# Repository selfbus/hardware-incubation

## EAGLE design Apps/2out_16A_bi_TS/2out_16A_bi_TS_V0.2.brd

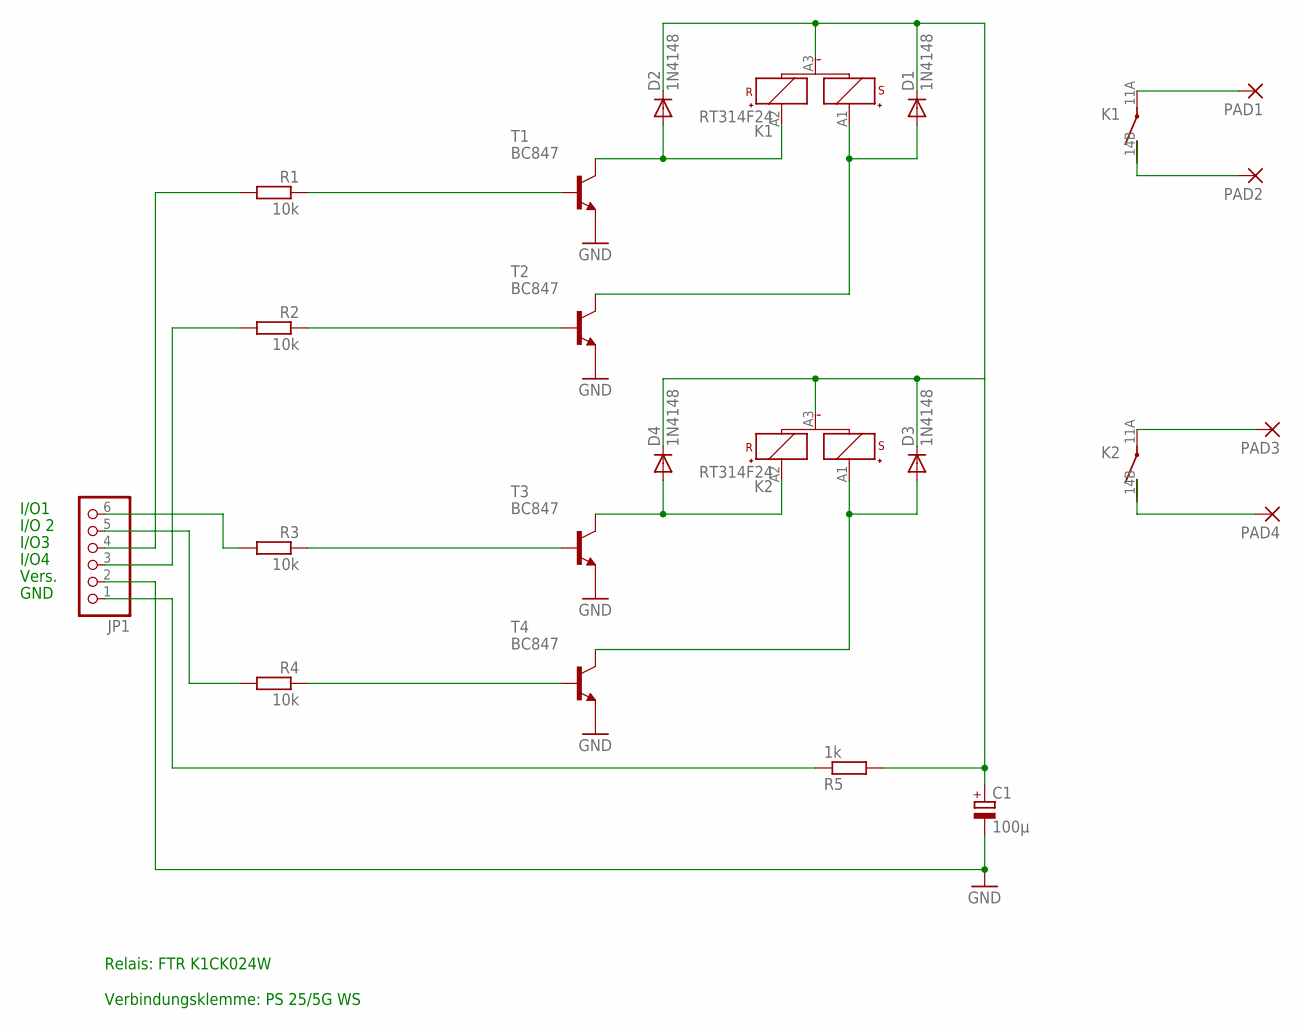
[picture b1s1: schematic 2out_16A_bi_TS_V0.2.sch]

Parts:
C1: 100µ; E3,5-8
D1, D2, D3, D4: 1N4148; MINIMELF
JP1: PINHD-1X6/90; 1X06/90
K1, K2: RT314F24; RT1-BI
PAD1, PAD2, PAD3, PAD4: 3,81/1,4
R1, R2, R3, R4: 10k; M1206
R5: 1k; M1206
T1, T2, T3, T4: BC847; SOT23

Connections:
GND: C1.-, JP1.2, T1.2 (E), T2.2 (E), T3.2 (E), T4.2 (E)
IO2: JP1.4, R1.2
unnamed: R2.1, T2.1 (B)
unnamed: JP1.3, R2.2
unnamed: K1.11A (PA), PAD1.1
unnamed: K1.14B (SA), PAD2.1
unnamed: K2.11A (PA), PAD3.1
unnamed: K2.14B (SA), PAD4.1
unnamed: JP1.6, R3.2
unnamed: R3.1, T3.1 (B)
unnamed: R4.1, T4.1 (B)
unnamed: JP1.5, R4.2
unnamed: R1.1, T1.1 (B)
unnamed: JP1.1, R5.1
R1: D1.A, K1.A1 (S+), T2.3 (C)
R2: D4.A, K2.A2 (R+), T3.3 (C)
R3: D2.A, K1.A2 (R+), T1.3 (C)
R4: D3.A, K2.A1 (S+), T4.3 (C)
VDD_IN: C1.+, D1.C, D2.C, D3.C, D4.C, K1.A3 (-), K2.A3 (-), R5.2

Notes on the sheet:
I/O1
Vers.
GND
Relais: FTR K1CK024W Verbindungsklemme: PS 25/5G WS
I/O 2
I/O3
I/O4

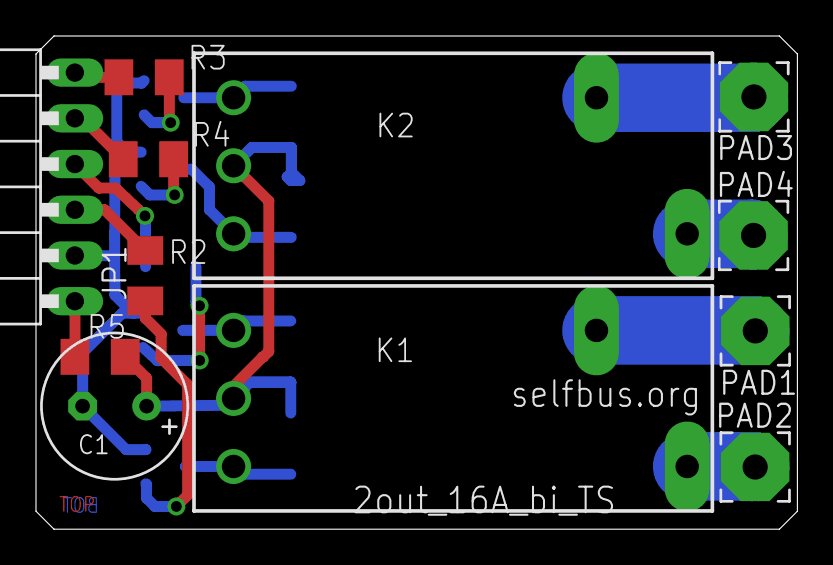
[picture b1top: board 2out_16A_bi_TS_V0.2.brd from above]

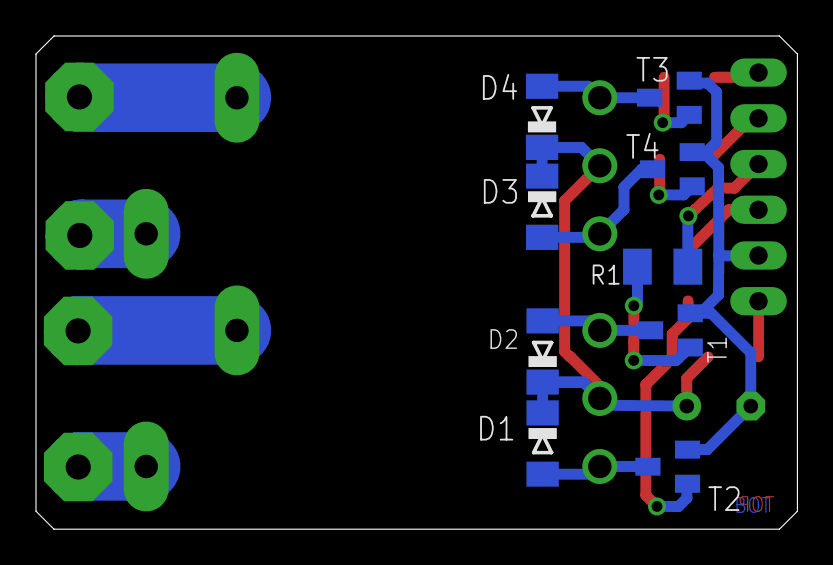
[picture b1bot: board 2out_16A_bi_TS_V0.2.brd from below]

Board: 2 copper layers, 42.3 x 27.4 mm, 21 parts (9 on the bottom side), 19 nets.

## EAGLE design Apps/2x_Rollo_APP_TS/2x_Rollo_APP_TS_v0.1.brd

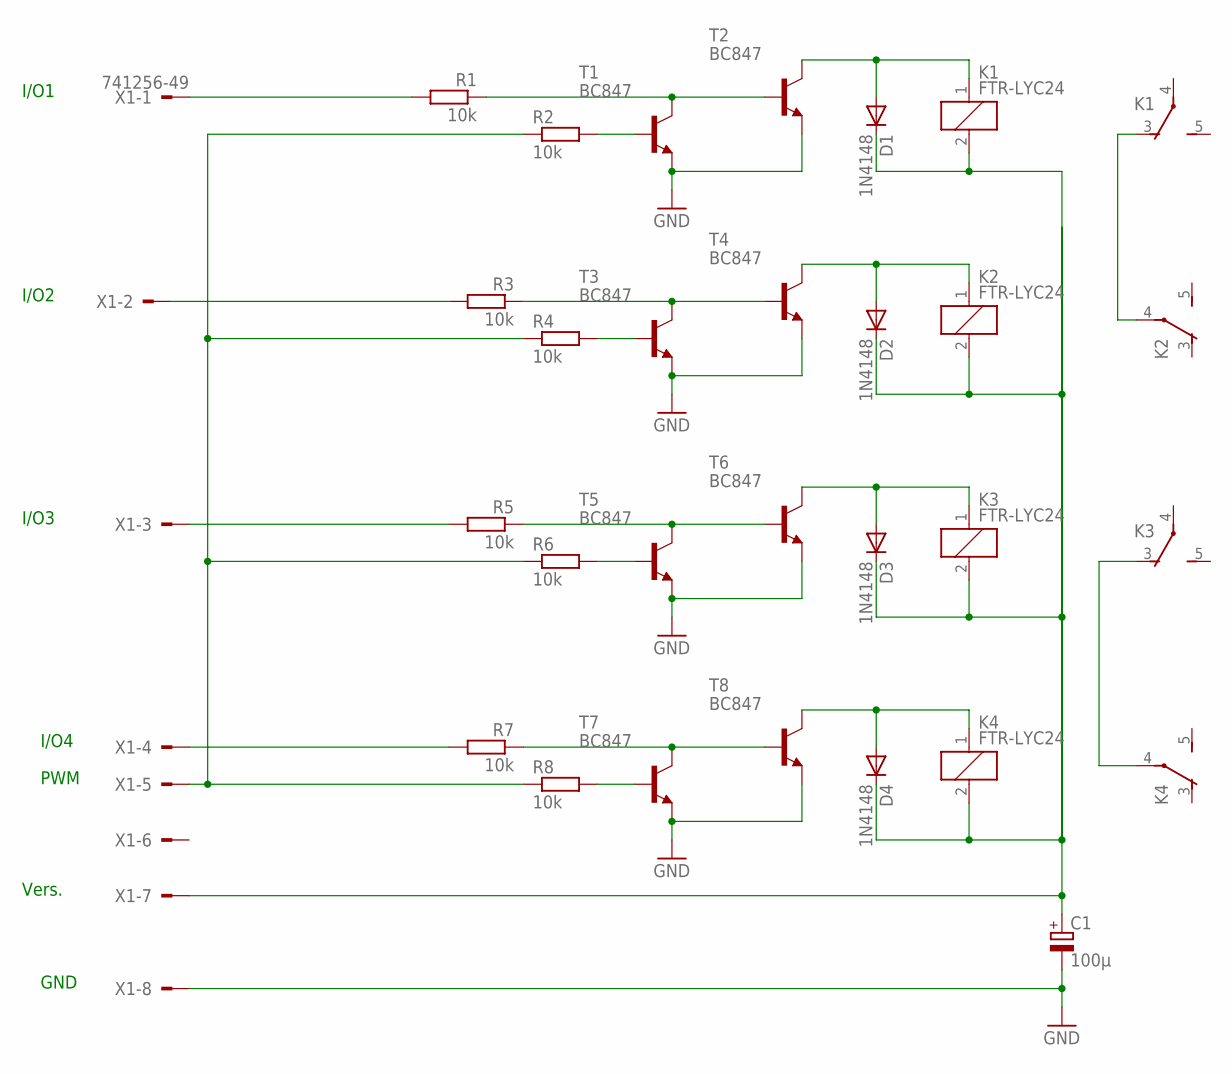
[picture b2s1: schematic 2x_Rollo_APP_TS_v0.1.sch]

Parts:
C1: 100µ; E2,5-6
D1, D2, D3, D4: 1N4148; MINIMELF
K1, K2, K3, K4: FTR-LYC24; FTR-LYC
R1, R2, R3, R4, R5, R6, R7, R8: 10k; M1206
T1, T2, T3, T4, T5, T6, T7, T8: BC847; SOT23
X1: 741256-49

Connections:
GND: C1.-, T1.2 (E), T2.2 (E), T3.2 (E), T4.2 (E), T5.2 (E), T6.2 (E), T7.2 (E), T8.2 (E), X1.8
unnamed: R1.2, X1.1
unnamed: R3.2, X1.2
unnamed: R2.1, R4.1, R6.1, R8.1, X1.5
unnamed: R3.1, T3.3 (C), T4.1 (B)
unnamed: R4.2, T3.1 (B)
unnamed: R5.2, X1.3
unnamed: R5.1, T5.3 (C), T6.1 (B)
unnamed: R6.2, T5.1 (B)
unnamed: R7.2, X1.4
unnamed: R1.1, T1.3 (C), T2.1 (B)
unnamed: R7.1, T7.3 (C), T8.1 (B)
unnamed: R8.2, T7.1 (B)
unnamed: R2.2, T1.1 (B)
unnamed: K3.3 (O), K4.4
unnamed: K1.3 (O), K2.4
R1: D2.A, K2.1, T4.3 (C)
R2: D3.A, K3.1, T6.3 (C)
R3: D1.A, K1.1, T2.3 (C)
R4: D4.A, K4.1, T8.3 (C)
VDD_IN1: C1.+, D1.C, D2.C, D3.C, D4.C, K1.2, K2.2, K3.2, K4.2, X1.7

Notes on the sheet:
PWM
I/O1
GND
Vers.
I/O2
I/O3
I/O4

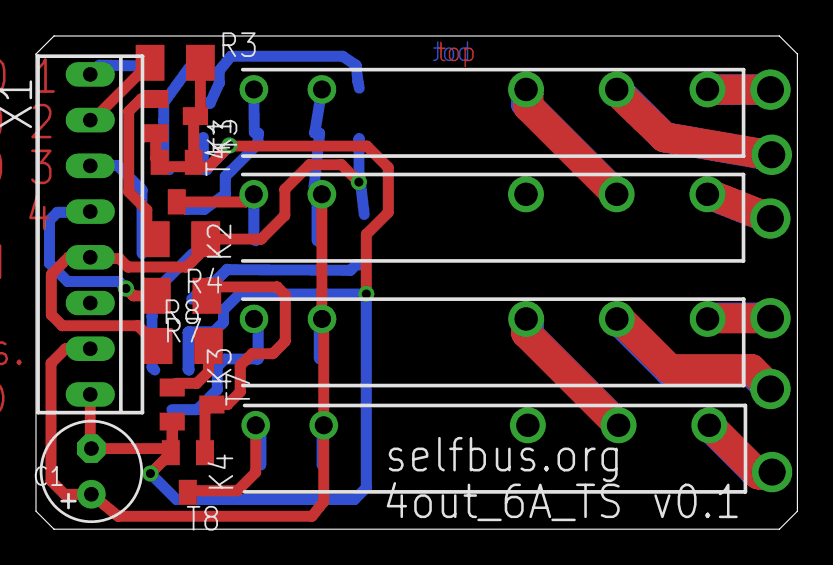
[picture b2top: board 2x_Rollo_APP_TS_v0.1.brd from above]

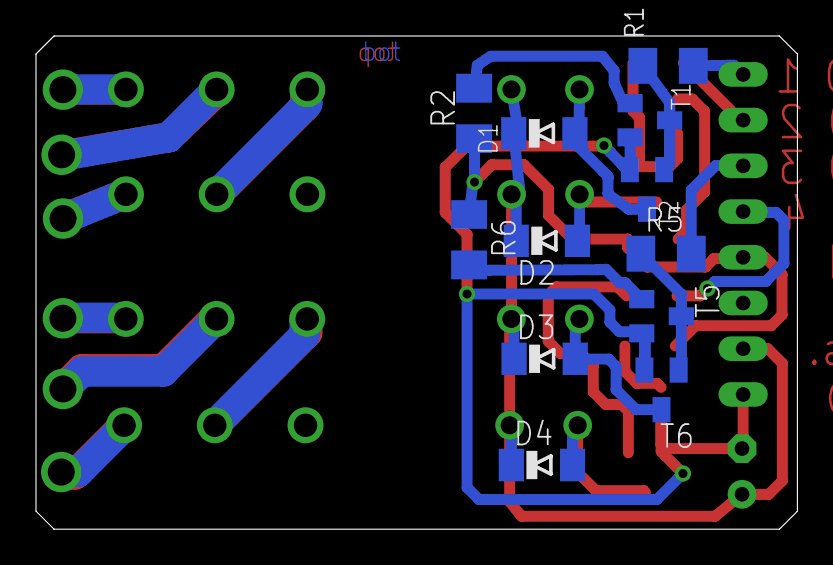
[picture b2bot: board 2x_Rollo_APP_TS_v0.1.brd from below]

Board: 2 copper layers, 42.3 x 27.4 mm, 26 parts (12 on the bottom side), 21 nets.

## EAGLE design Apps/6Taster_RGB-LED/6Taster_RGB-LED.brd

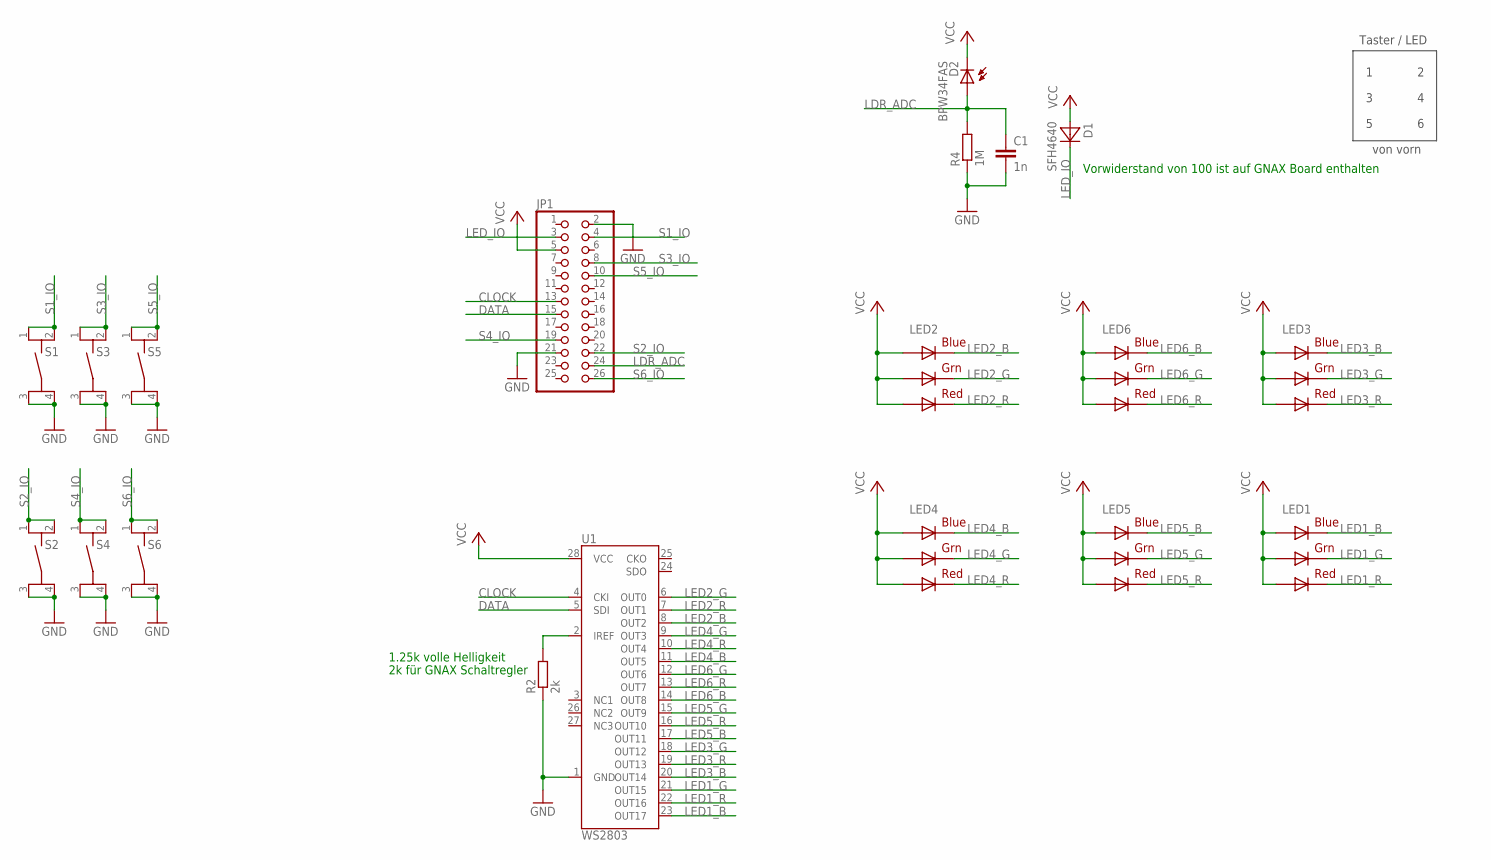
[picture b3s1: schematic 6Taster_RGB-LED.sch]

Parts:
C1: 1n; C0805
D1: SFH4640
D2: BPW34FAS
JP1: PINHD-2X13_2.54-SMD; 2X13SMD
LED1, LED2, LED3, LED4, LED5, LED6: RGB; RGBLED5050
R2: 2k; R0805
R4: 1M; R0805
S1, S2, S3, S4, S5, S6: TASTER_9314SMD; TASTER_9314
U1: WS2803; SOP-28

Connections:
CLOCK: JP1.13, U1.4 (CKI)
DATA: JP1.15, U1.5 (SDI)
GND: C1.2, JP1.2, JP1.21, R2.1, R4.1, S1.3, S1.4, S2.3, S2.4, S3.3, S3.4, S4.3, S4.4, S5.3, S5.4, S6.3, S6.4, U1.1 (GND)
LDR_ADC: C1.1, D2.ANODE (A), JP1.24, R4.2
LED1_B: LED1.4 (BLUE_C), U1.23 (OUT17)
LED1_G: LED1.6 (GREEN_C), U1.21 (OUT15)
LED1_R: LED1.5 (RED_C), U1.22 (OUT16)
LED2_B: LED2.4 (BLUE_C), U1.8 (OUT2)
LED2_G: LED2.6 (GREEN_C), U1.6 (OUT0)
LED2_R: LED2.5 (RED_C), U1.7 (OUT1)
LED3_B: LED3.4 (BLUE_C), U1.20 (OUT14)
LED3_G: LED3.6 (GREEN_C), U1.18 (OUT12)
LED3_R: LED3.5 (RED_C), U1.19 (OUT13)
LED4_B: LED4.4 (BLUE_C), U1.11 (OUT5)
LED4_G: LED4.6 (GREEN_C), U1.9 (OUT3)
LED4_R: LED4.5 (RED_C), U1.10 (OUT4)
LED5_B: LED5.4 (BLUE_C), U1.17 (OUT11)
LED5_G: LED5.6 (GREEN_C), U1.15 (OUT9)
LED5_R: LED5.5 (RED_C), U1.16 (OUT10)
LED6_B: LED6.4 (BLUE_C), U1.14 (OUT8)
LED6_G: LED6.6 (GREEN_C), U1.12 (OUT6)
LED6_R: LED6.5 (RED_C), U1.13 (OUT7)
LED_IO: D1.KATHODE (C), JP1.3
unnamed: R2.2, U1.2 (IREF)
S1_IO: JP1.4, S1.1, S1.2
S2_IO: JP1.22, S2.1, S2.2
S3_IO: JP1.8, S3.1, S3.2
S4_IO: JP1.19, S4.1, S4.2
S5_IO: JP1.10, S5.1, S5.2
S6_IO: JP1.26, S6.1, S6.2
VCC: D1.ANODE (A), D2.KATHODE (C), JP1.5, LED1.1 (GREEN_A), LED1.2 (RED_A), LED1.3 (BLUE_A), LED2.1 (GREEN_A), LED2.2 (RED_A), LED2.3 (BLUE_A), LED3.1 (GREEN_A), LED3.2 (RED_A), LED3.3 (BLUE_A), LED4.1 (GREEN_A), LED4.2 (RED_A), LED4.3 (BLUE_A), LED5.1 (GREEN_A), LED5.2 (RED_A), LED5.3 (BLUE_A), LED6.1 (GREEN_A), LED6.2 (RED_A), LED6.3 (BLUE_A), U1.28 (VCC)

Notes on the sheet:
Taster / LED
von vorn
Vorwiderstand von 100 ist auf GNAX Board enthalten
1.25k volle Helligkeit
2k für GNAX Schaltregler

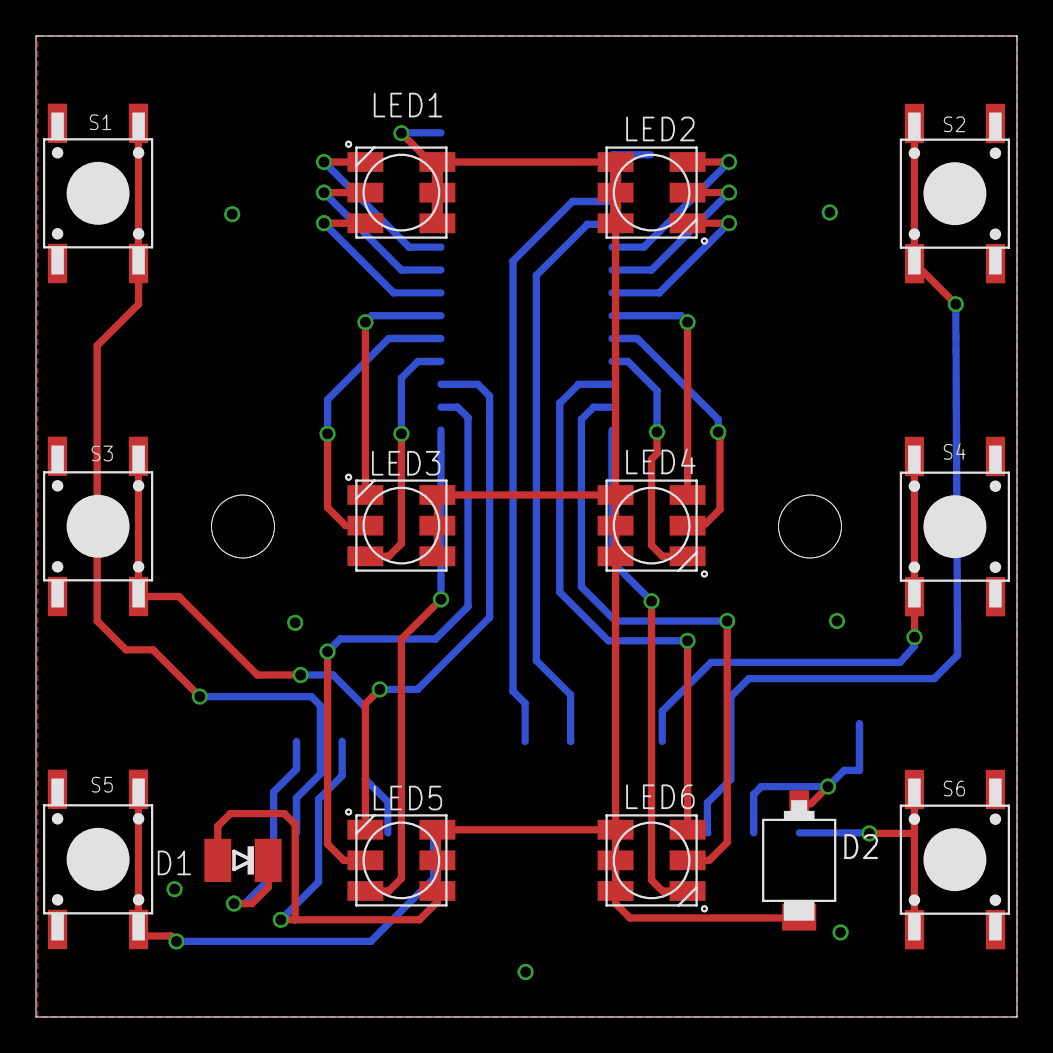
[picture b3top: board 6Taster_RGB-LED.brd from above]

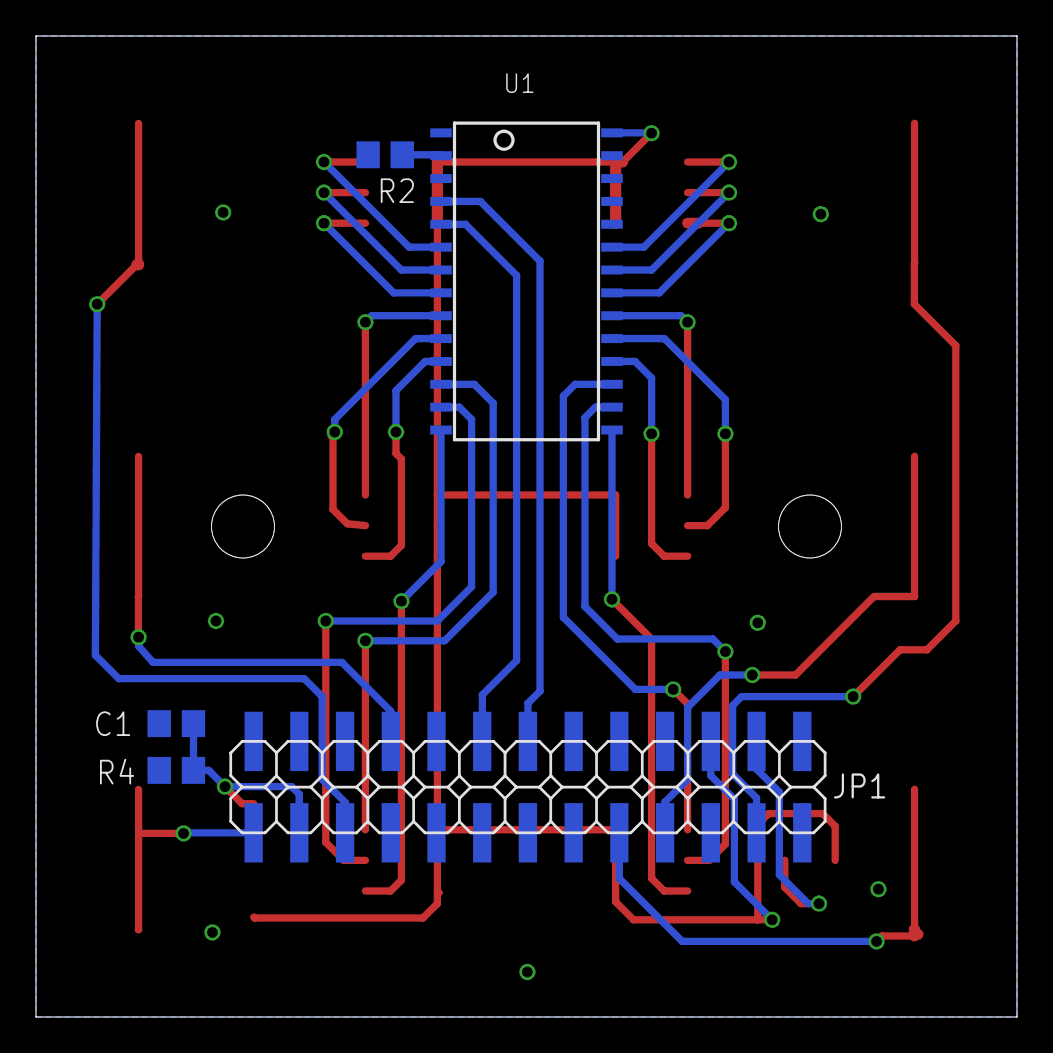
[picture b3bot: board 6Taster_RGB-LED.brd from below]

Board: 2 copper layers, 54.5 x 54.5 mm, 19 parts (5 on the bottom side), 31 nets.
